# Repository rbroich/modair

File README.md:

# ModAir
Modular Aviation Instruments - Open Source Avionics for Microlights and other Non-Type-Certified Aircraft

For documentation and details refer to the Hackaday.io Project Page [ModAir - Modular Aviation Instruments](https://hackaday.io/project/19325)

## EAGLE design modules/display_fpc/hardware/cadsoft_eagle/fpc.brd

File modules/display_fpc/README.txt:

ERC240160_ENCLOSURE

rotary encoder: solder ribbon cable
(mounted to PCB would have insufficient reach, and mechanically difficult to insert with the LCD FPC soldered on already)

add SPDT switch on left side
and LED?

Fine grid sand paper on top
Printed front panel labels on thick transparency (guerrilla glass?)
-black portions to cover 3d printed inconsistencies

PCB:
-no components on bottom side, besides BUS connector
-header for LCD backlight
-LCD FPC footprint directly below LCD, inline with edge of LCD frame
-header for rotary encoder
-solder pads for switch
-electrolytic caps mounted sideways

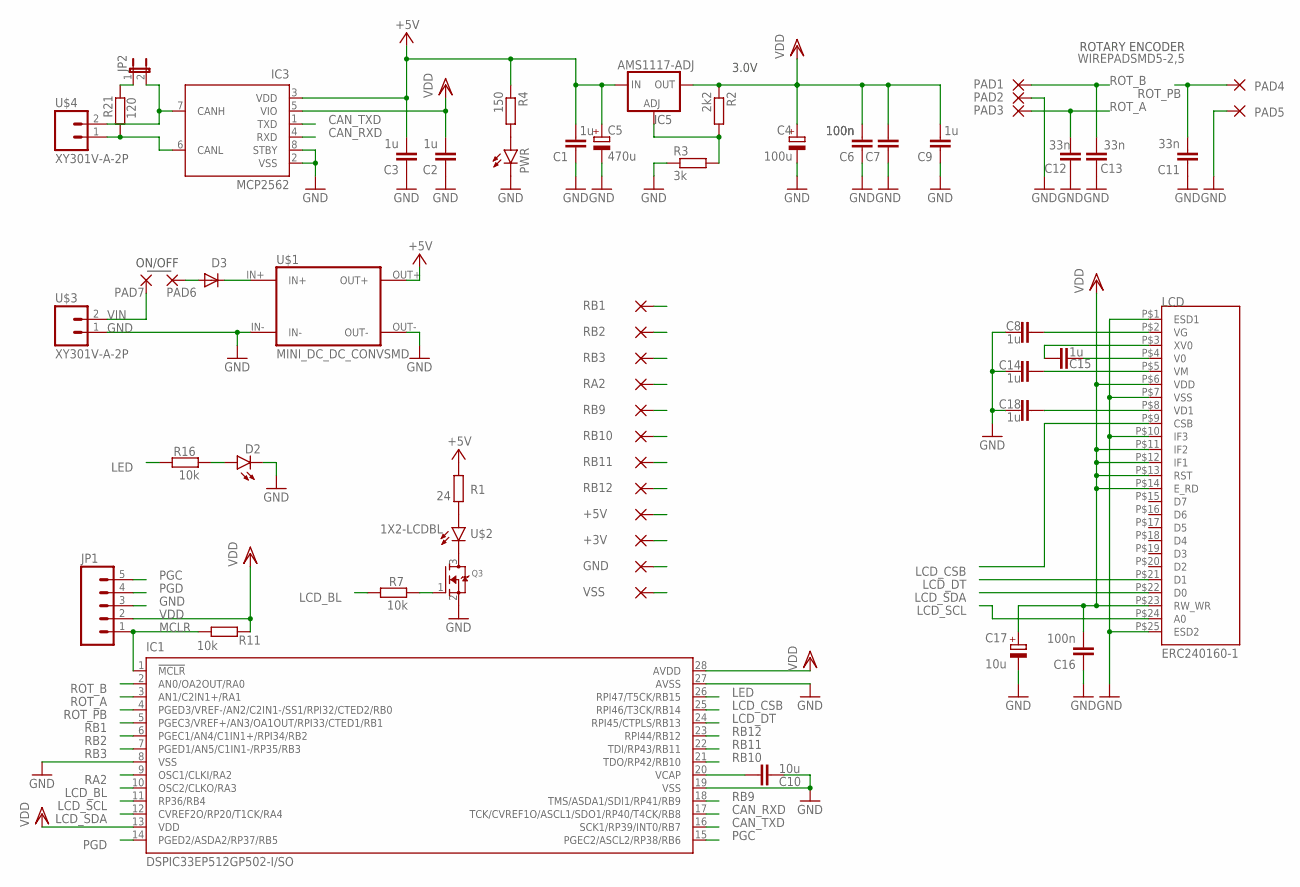
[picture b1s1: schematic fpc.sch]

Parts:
+3V, +5V: WIREPADSMD1,27-254; SMD1,27-2,54
C1, C2, C3, C8, C9, C14, C15, C18: 1u; C0603K
C4: 100u; SANYO-OSCON_SMD_B6
C5: 470u; SANYO-OSCON_SMD_B6
C6, C7, C16: 100n; C0603K
C10: 10u; C0805
C11, C12, C13: 33n; C0603K
C17: 10u; SANYO-OSCON_SMD_E12
D2: LED-FKIT-1206; FKIT-LED-1206
D3: DIODESMA; SMADIODE
GND: WIREPADSMD1,27-254; SMD1,27-2,54
IC1: DSPIC33EP512GP502-I/SO; SO28W
IC3: MCP2562; SO-08
IC5: AMS1117-ADJ; SOT223
JP1: M05PTH; 1X05
JP2: JP1E; JP1
LCD: ERC240160-1; 1X25-LCDFPC-SMD
PAD1, PAD2, PAD3, PAD4, PAD5, PAD6, PAD7: WIREPADSMD5-2,5; 5-2,5
PWR: LED-FKIT-1206; FKIT-LED-1206
Q3: MOSFET-NREFLOW; SOT23
R1: 24; R0805
R2: 2k2; R0603
R3: 3k; R0603
R4: 150; R0603
R7, R11, R16: 10k; R0603
R21: 120; R0603
RA2: WIREPADSMD1,27-254; SMD1,27-2,54
RB1, RB2, RB3, RB9, RB10, RB11, RB12: WIREPADSMD1,27-254; SMD1,27-2,54
U$1: MINI_DC_DC_CONVSMD; DSN-MINI-360-SMD
U$2: 1X2-LCDBL; 1X2-LCDBL-SMD
U$3, U$4: XY301V-A-2P
VSS: WIREPADSMD1,27-254; SMD1,27-2,54

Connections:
+5V: +5V.1, C1.2, C3.2, C5.+, IC3.3 (VDD), IC5.3 (IN), R1.1, R4.1, U$1.OUT+
CAN_H: IC3.7 (CANH), JP2.2, U$4.2
CAN_L: IC3.6 (CANL), R21.1, U$4.1
CAN_RXD: IC1.17 (TCK/CVREF1O/ASCL1/SDO1/RP40/T4CK/RB8), IC3.4 (RXD)
CAN_TXD: IC1.16 (SCK1/RP39/INT0/RB7), IC3.1 (TXD)
GND: C1.1, C2.1, C3.1, C4.-, C5.-, C6.1, C7.1, C8.1, C9.1, C10.1, C11.1, C12.1, C13.1, C14.1, C16.1, C17.-, C18.1, D2.C, GND.1, IC1.8 (VSS), IC1.19 (VSS), IC1.27 (AVSS), IC3.2 (VSS), IC3.8 (STBY), JP1.3, LCD.P$1 (ESD1), LCD.P$7 (VSS), LCD.P$10 (IF3), LCD.P$25 (ESD2), PAD2.1, PAD5.1, PWR.C, Q3.2 (S), R3.1, U$1.IN-, U$1.OUT-, U$3.1, VSS.1
LCD_BL: IC1.10 (OSC2/CLKO/RA3), R7.2
LCD_CSB: IC1.25 (RPI46/T3CK/RB14), LCD.P$9 (CSB)
LCD_DT: IC1.24 (RPI45/CTPLS/RB13), LCD.P$21 (D1)
LCD_SCL: IC1.11 (RP36/RB4), LCD.P$24 (A0)
LCD_SDA: IC1.12 (CVREF2O/RP20/T1CK/RA4), LCD.P$22 (D0)
LED: IC1.26 (RPI47/T5CK/RB15), R16.2
MCLR: IC1.1 (!MCLR!), JP1.1, R11.2
unnamed: Q3.1 (G), R7.1
unnamed: R1.2, U$2.A
unnamed: PWR.A, R4.2
unnamed: Q3.3 (D), U$2.K (C)
unnamed: C15.2, LCD.P$4 (V0)
unnamed: C15.1, LCD.P$3 (XV0)
unnamed: C8.2, LCD.P$2 (VG)
unnamed: C14.2, LCD.P$5 (VM)
unnamed: D2.A, R16.1
unnamed: C18.2, LCD.P$8 (VD1)
unnamed: IC5.1 (ADJ), R2.2, R3.2
unnamed: D3.A, PAD6.1
unnamed: JP2.1, R21.2
PGC: IC1.15 (PGEC2/ASCL2/RP38/RB6), JP1.5
PGD: IC1.14 (PGED2/ASDA2/RP37/RB5), JP1.4
RA2: IC1.9 (OSC1/CLKI/RA2), RA2.1
RB1: IC1.5 (PGEC3/VREF+/AN3/OA1OUT/RPI33/CTED1/RB1), RB1.1
RB2: IC1.6 (PGEC1/AN4/C1IN1+/RPI34/RB2), RB2.1
RB3: IC1.7 (PGED1/AN5/C1IN1-/RP35/RB3), RB3.1
RB9: IC1.18 (TMS/ASDA1/SDI1/RP41/RB9), RB9.1
RB10: IC1.21 (TDO/RP42/RB10), RB10.1
RB11: IC1.22 (TDI/RP43/RB11), RB11.1
RB12: IC1.23 (RPI44/RB12), RB12.1
ROT_A: C12.2, IC1.3 (AN1/C2IN1+/RA1), PAD3.1
ROT_B: C13.2, IC1.2 (AN0/OA2OUT/RA0), PAD1.1
ROT_PB: C11.2, IC1.4 (PGED3/VREF-/AN2/C2IN1-/SS1/RPI32/CTED2/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), PAD4.1
VCAP: C10.2, IC1.20 (VCAP)
VDD: +3V.1, C2.2, C4.+, C6.2, C7.2, C9.2, C16.2, C17.+, IC1.13 (VDD), IC1.28 (AVDD), IC3.5 (VIO), IC5.2 (OUT), IC5.@2 (OUT), JP1.2, LCD.P$6 (VDD), LCD.P$11 (IF2), LCD.P$12 (IF1), LCD.P$13 (RST), LCD.P$14 (E_RD), LCD.P$23 (RW_WR), R2.1, R11.1
VIN: PAD7.1, U$3.2
VIN_D: D3.C, U$1.IN+

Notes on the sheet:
3.0V
ON/OFF
ROTARY ENCODER

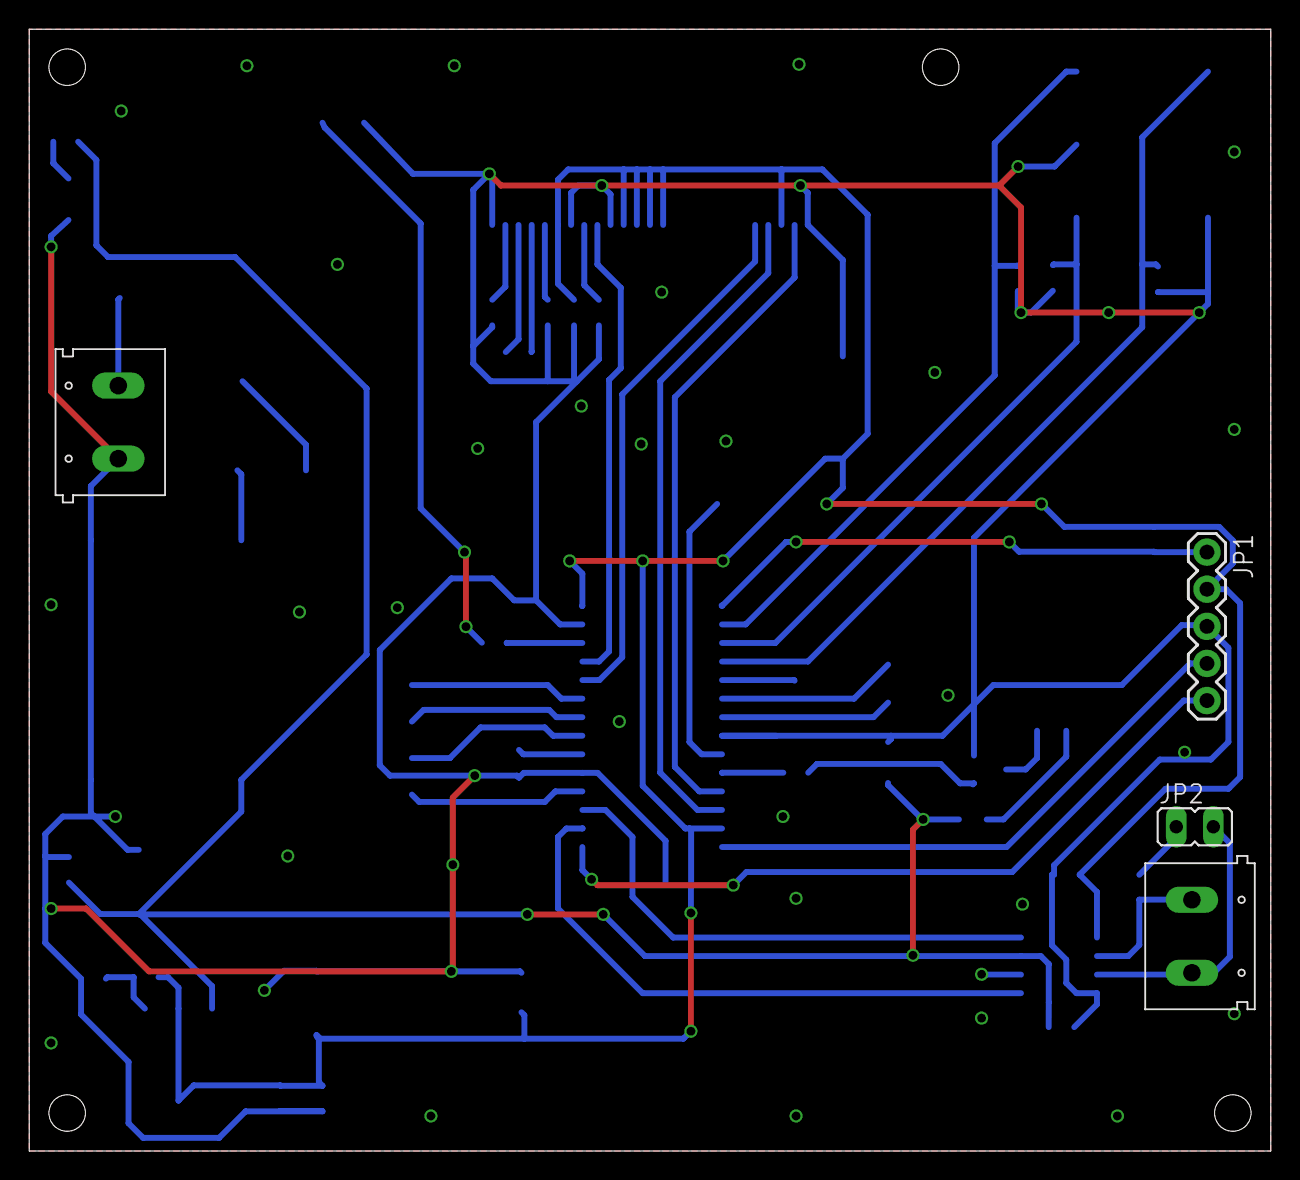
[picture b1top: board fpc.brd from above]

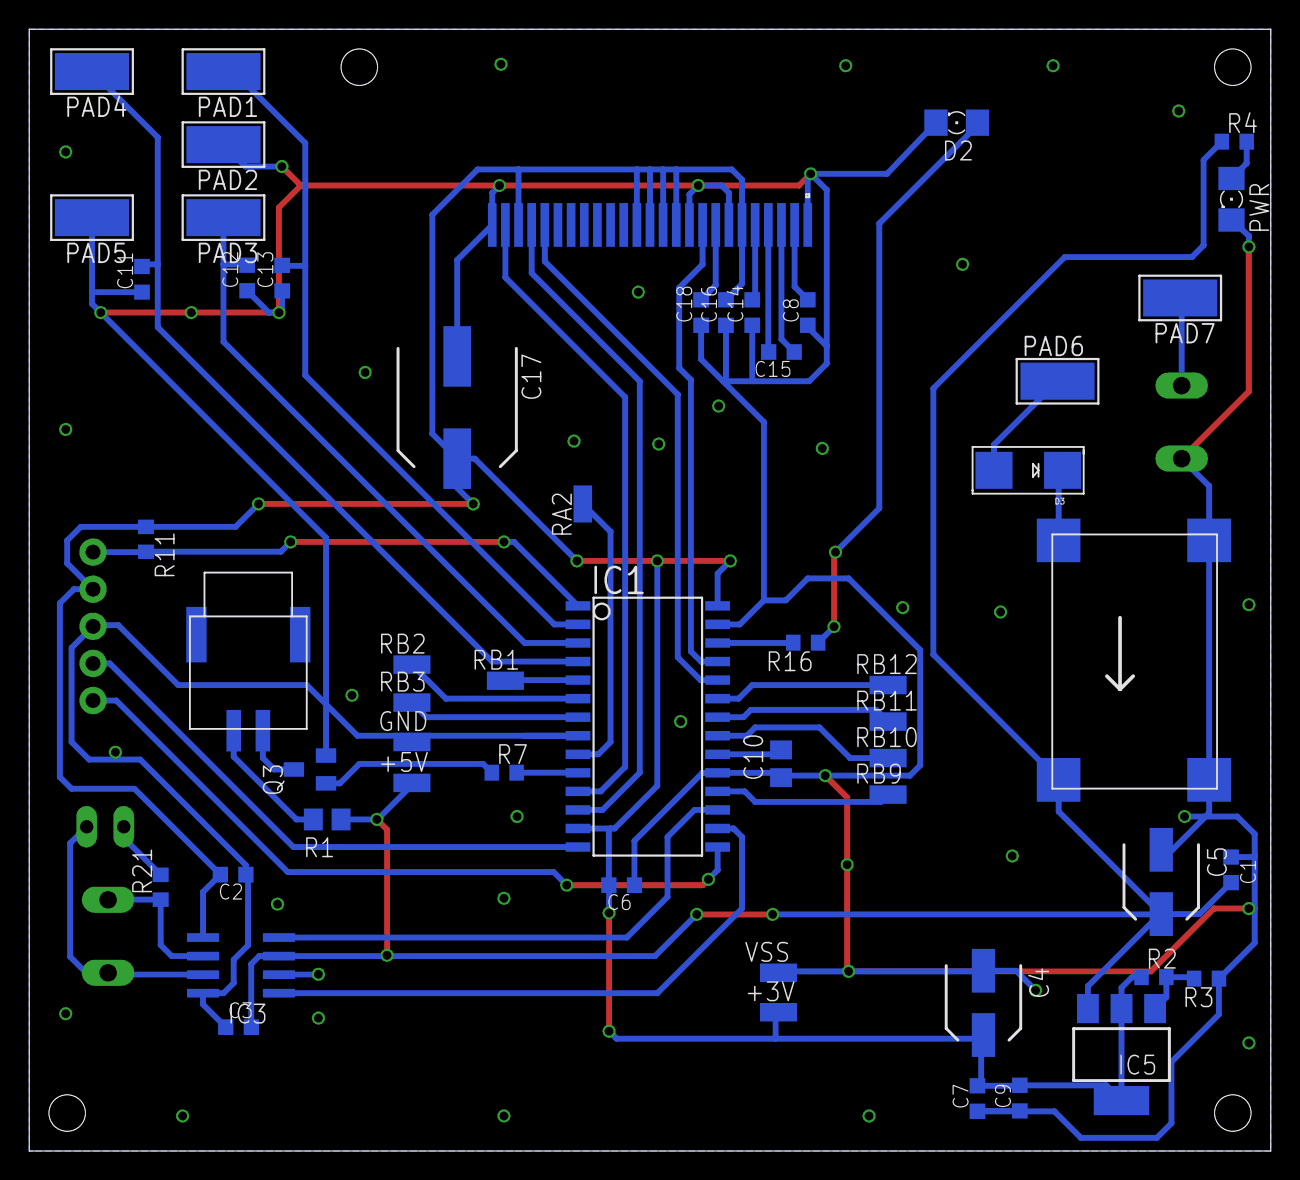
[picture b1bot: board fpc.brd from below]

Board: 2 copper layers, 85.0 x 76.8 mm, 59 parts (55 on the bottom side), 43 nets.

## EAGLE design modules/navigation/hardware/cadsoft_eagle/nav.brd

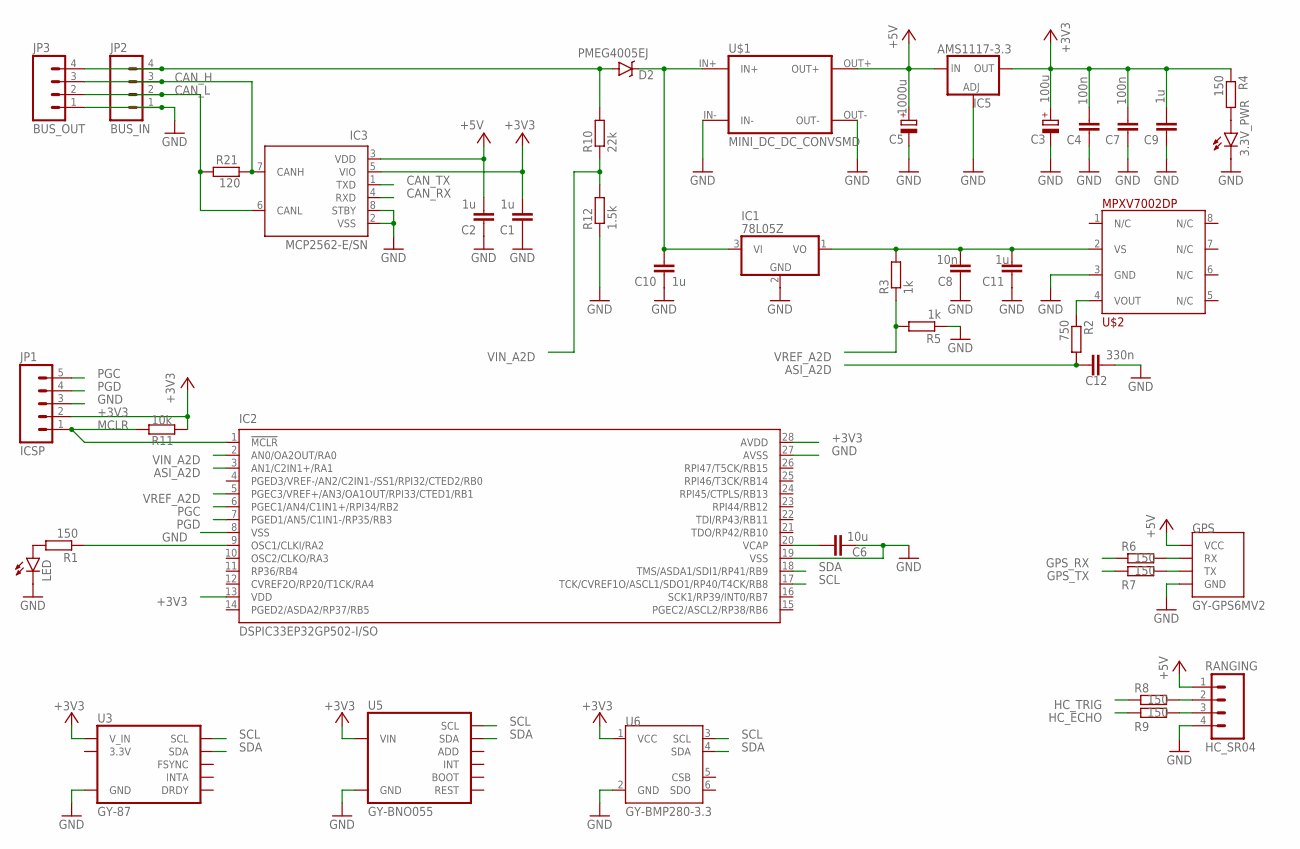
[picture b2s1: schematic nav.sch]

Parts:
3.3V_PWR: LED-FKIT-1206; FKIT-LED-1206
C1, C2, C11: 1u; C0603K
C3: 100u; E2,5-7
C4, C7: 100n; C0603K
C5: 1000u; E3,5-8
C6: 10u; C0805K
C8: 10n; C0603K
C9, C10: 1u; C0603
C12: 330n; C0603K
D2: PMEG4005EJ; SOD-323
GPS: GY-GPS6MV2
IC1: 78L05Z; TO92
IC2: DSPIC33EP32GP502-I/SO; SO28W
IC3: MCP2562-E/SN; SO-08
IC5: AMS1117-3.3; SOT223
JP1: ICSP; 1X05
JP2: BUS_IN; 1X04
JP3: BUS_OUT; 1X04
LED: LED-FKIT-1206; FKIT-LED-1206
R1, R4, R6, R7, R8, R9: 150; R0603
R2: 750; R0603
R3, R5: 1k; R0603
R10: 22k; R0603
R11: 10k; R0603
R12: 1.5k; R0603
R21: 120; R0603
RANGING: HC_SR04; 1X04
U3: GY-87
U5: GY-BNO055
U6: GY-BMP280-3.3
U$1: MINI_DC_DC_CONVSMD; DSN-MINI-360-SMD
U$2: MPXV7002DP

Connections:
3.3V: U3.3.3V
+3V3: C1.2, C3.+, C4.2, C7.2, C9.2, IC2.13 (VDD), IC2.28 (AVDD), IC3.5 (VIO), IC5.2 (OUT), IC5.@2 (OUT), JP1.2, R4.1, R11.1, U3.VCC_IN (V_IN), U5.VIN, U6.1 (VCC)
+5V: C2.2, C5.+, GPS.VCC, IC3.3 (VDD), IC5.3 (IN), RANGING.1, U$1.OUT+
ASI_A2D: C12.2, IC2.3 (AN1/C2IN1+/RA1), R2.2
CAN_H: IC3.7 (CANH), JP2.3, JP3.3, R21.2
CAN_L: IC3.6 (CANL), JP2.2, JP3.2, R21.1
CAN_RX: IC3.4 (RXD)
CAN_TX: IC3.1 (TXD)
GND: 3.3V_PWR.C, C1.1, C2.1, C3.-, C4.1, C5.-, C6.1, C7.1, C8.1, C9.1, C10.1, C11.1, C12.1, GPS.GND, IC1.2 (GND), IC2.8 (VSS), IC2.19 (VSS), IC2.27 (AVSS), IC3.2 (VSS), IC3.8 (STBY), IC5.1 (ADJ), JP1.3, JP2.1, JP3.1, LED.C, R5.1, R12.1, RANGING.4, U3.GND, U5.GND, U6.2 (GND), U$1.IN-, U$1.OUT-, U$2.3 (GND)
GPS_RX: R6.1
GPS_TX: R7.1
HC_ECHO: R9.1
HC_TRIG: R8.1
MCLR: IC2.1 (!MCLR!), JP1.1, R11.2
unnamed: C8.2, C11.2, IC1.1 (VO), R3.2, U$2.2 (VS)
unnamed: GPS.RX, R6.2
unnamed: 3.3V_PWR.A, R4.2
unnamed: LED.A, R1.2
unnamed: R2.1, U$2.4 (VOUT)
unnamed: GPS.TX, R7.2
unnamed: R8.2, RANGING.2
unnamed: R9.2, RANGING.3
unnamed: IC2.9 (OSC1/CLKI/RA2), R1.1
PGC: IC2.6 (PGEC1/AN4/C1IN1+/RPI34/RB2), JP1.5
PGD: IC2.7 (PGED1/AN5/C1IN1-/RP35/RB3), JP1.4
SCL: IC2.17 (TCK/CVREF1O/ASCL1/SDO1/RP40/T4CK/RB8), U3.SCL, U5.SCL, U6.3 (SCL)
SDA: IC2.18 (TMS/ASDA1/SDI1/RP41/RB9), U3.SDA, U5.SDA, U6.4 (SDA)
VCAP: C6.2, IC2.20 (VCAP)
VIN: D2.A, JP2.4, JP3.4, R10.2
VIN_A2D: IC2.2 (AN0/OA2OUT/RA0), R10.1, R12.2
VIN_D: C10.2, D2.C, IC1.3 (VI), U$1.IN+
VREF_A2D: IC2.5 (PGEC3/VREF+/AN3/OA1OUT/RPI33/CTED1/RB1), R3.1, R5.2

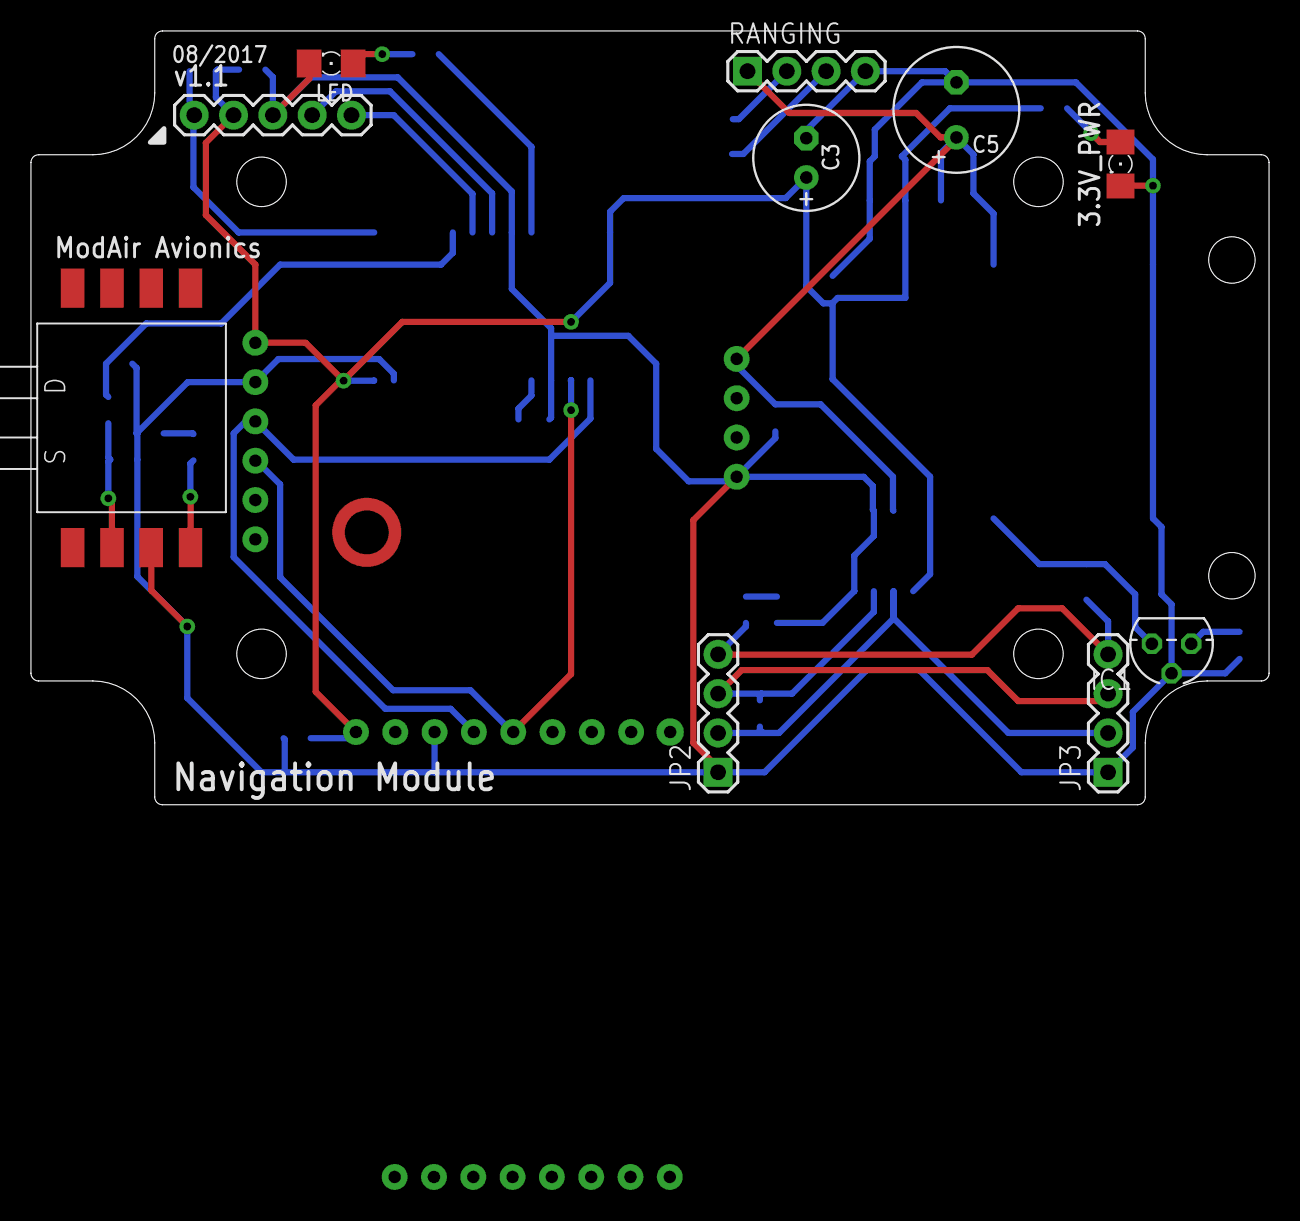
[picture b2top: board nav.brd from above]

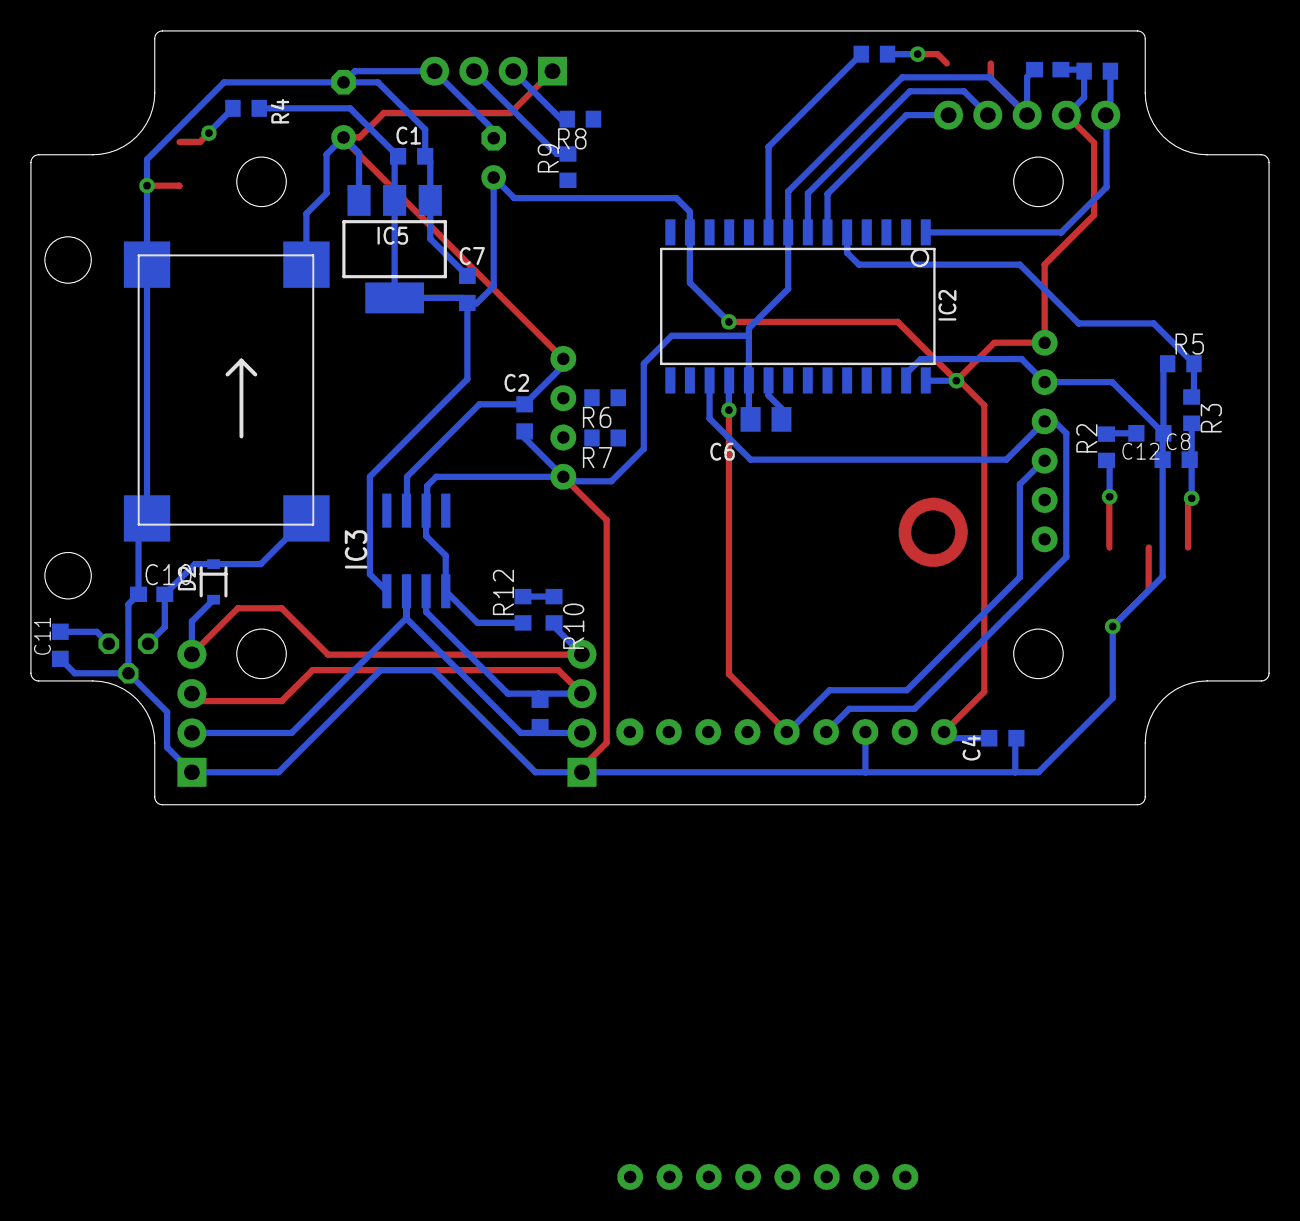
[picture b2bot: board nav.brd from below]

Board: 2 copper layers, 80.0 x 50.0 mm, 42 parts (29 on the bottom side), 25 nets.

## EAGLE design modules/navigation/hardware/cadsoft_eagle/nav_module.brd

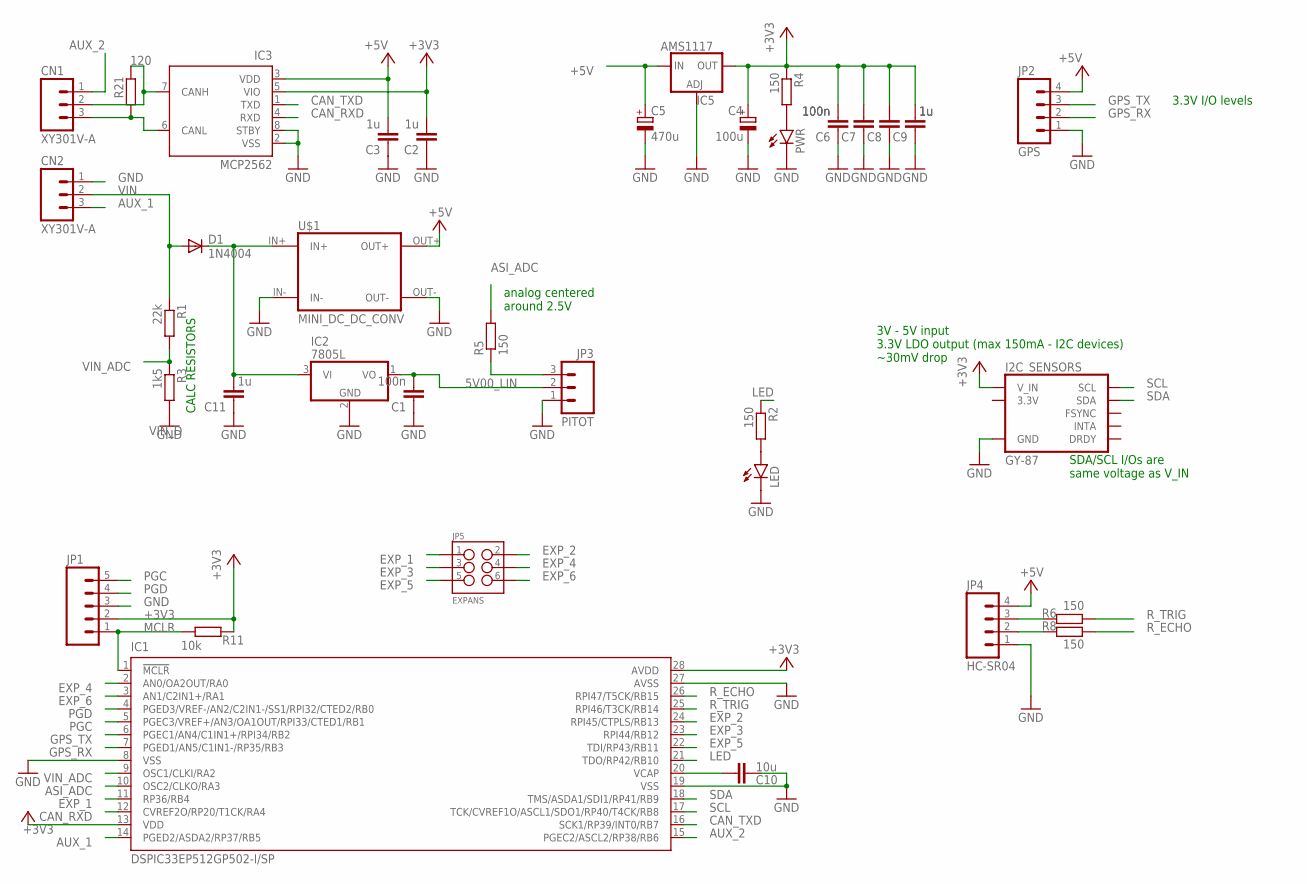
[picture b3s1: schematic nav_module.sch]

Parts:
C1, C6, C7: 100n; C0603K
C2, C3, C8, C9, C11: 1u; C0603K
C4: 100u; E2,5-7
C5: 470u; E3,5-8
C10: 10u; C025-030X050
CN1, CN2: XY301V-A
D1: 1N4004; DO41-10
I2C_SENSORS: GY-87
IC1: DSPIC33EP512GP502-I/SP; DIL28-3
IC2: 7805L; TO92
IC3: MCP2562; DIL8
IC5: AMS1117; SOT223
JP1: M05PTH; 1X05
JP2: GPS; 1X04
JP3: PITOT; 1X03
JP4: HC-SR04; 1X04
JP5: EXPANS; 2X3
LED: LED-FKIT-1206; FKIT-LED-1206
PWR: LED-FKIT-1206; FKIT-LED-1206
R1: 22k; R0603
R2, R4, R5, R6, R8: 150; R0603
R3: 1k5; R0603
R11: 10k; R0603
R21: 120; R0603
U$1: MINI_DC_DC_CONV; DSN-MINI-360

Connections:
3.3V: I2C_SENSORS.3.3V
5V00_LIN: C1.2, IC2.1 (VO), JP3.2
+3V3: C2.2, C4.+, C6.2, C7.2, C8.2, C9.2, I2C_SENSORS.VCC_IN (V_IN), IC1.13 (VDD), IC1.28 (AVDD), IC3.5 (VIO), IC5.2 (OUT), IC5.@2 (OUT), JP1.2, R4.1, R11.1
+5V: C3.2, C5.+, IC3.3 (VDD), IC5.3 (IN), JP2.4, JP4.4, U$1.OUT+
ASI: JP3.3, R5.1
ASI_ADC: IC1.10 (OSC2/CLKO/RA3), R5.2
AUX_1: CN2.3, IC1.14 (PGED2/ASDA2/RP37/RB5)
AUX_2: CN1.1, IC1.15 (PGEC2/ASCL2/RP38/RB6)
CAN_H: CN1.2, IC3.7 (CANH), R21.2
CAN_L: CN1.3, IC3.6 (CANL), R21.1
CAN_RXD: IC1.12 (CVREF2O/RP20/T1CK/RA4), IC3.4 (RXD)
CAN_TXD: IC1.16 (SCK1/RP39/INT0/RB7), IC3.1 (TXD)
EXP_1: IC1.11 (RP36/RB4), JP5.1
EXP_2: IC1.24 (RPI45/CTPLS/RB13), JP5.2
EXP_3: IC1.23 (RPI44/RB12), JP5.3
EXP_4: IC1.2 (AN0/OA2OUT/RA0), JP5.4
EXP_5: IC1.22 (TDI/RP43/RB11), JP5.5
EXP_6: IC1.3 (AN1/C2IN1+/RA1), JP5.6
GND: C1.1, C2.1, C3.1, C4.-, C5.-, C6.1, C7.1, C8.1, C9.1, C10.1, C11.1, CN2.1, I2C_SENSORS.GND, IC1.8 (VSS), IC1.19 (VSS), IC1.27 (AVSS), IC2.2 (GND), IC3.2 (VSS), IC3.8 (STBY), IC5.1 (ADJ), JP1.3, JP2.1, JP3.1, JP4.1, LED.C, PWR.C, R3.2, U$1.IN-, U$1.OUT-
GPS_RX: IC1.7 (PGED1/AN5/C1IN1-/RP35/RB3), JP2.2
GPS_TX: IC1.6 (PGEC1/AN4/C1IN1+/RPI34/RB2), JP2.3
HS_ECHO: JP4.2, R8.1
HS_TRIG: JP4.3, R6.2
LED: IC1.21 (TDO/RP42/RB10), R2.1
MCLR: IC1.1 (!MCLR!), JP1.1, R11.2
unnamed: PWR.A, R4.2
unnamed: LED.A, R2.2
PGC: IC1.5 (PGEC3/VREF+/AN3/OA1OUT/RPI33/CTED1/RB1), JP1.5
PGD: IC1.4 (PGED3/VREF-/AN2/C2IN1-/SS1/RPI32/CTED2/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), JP1.4
R_ECHO: IC1.26 (RPI47/T5CK/RB15), R8.2
R_TRIG: IC1.25 (RPI46/T3CK/RB14), R6.1
SCL: I2C_SENSORS.SCL, IC1.17 (TCK/CVREF1O/ASCL1/SDO1/RP40/T4CK/RB8)
SDA: I2C_SENSORS.SDA, IC1.18 (TMS/ASDA1/SDI1/RP41/RB9)
VCAP: C10.2, IC1.20 (VCAP)
VIN: CN2.2, D1.A, R1.1
VIN_ADC: IC1.9 (OSC1/CLKI/RA2), R1.2, R3.1
VIN_D: C11.2, D1.C, IC2.3 (VI), U$1.IN+

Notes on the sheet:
3V - 5V input 3.3V LDO output (max 150mA - I2C devices) ~30mV drop
SDA/SCL I/Os are same voltage as V_IN
3.3V I/O levels
analog centered around 2.5V
CALC RESISTORS

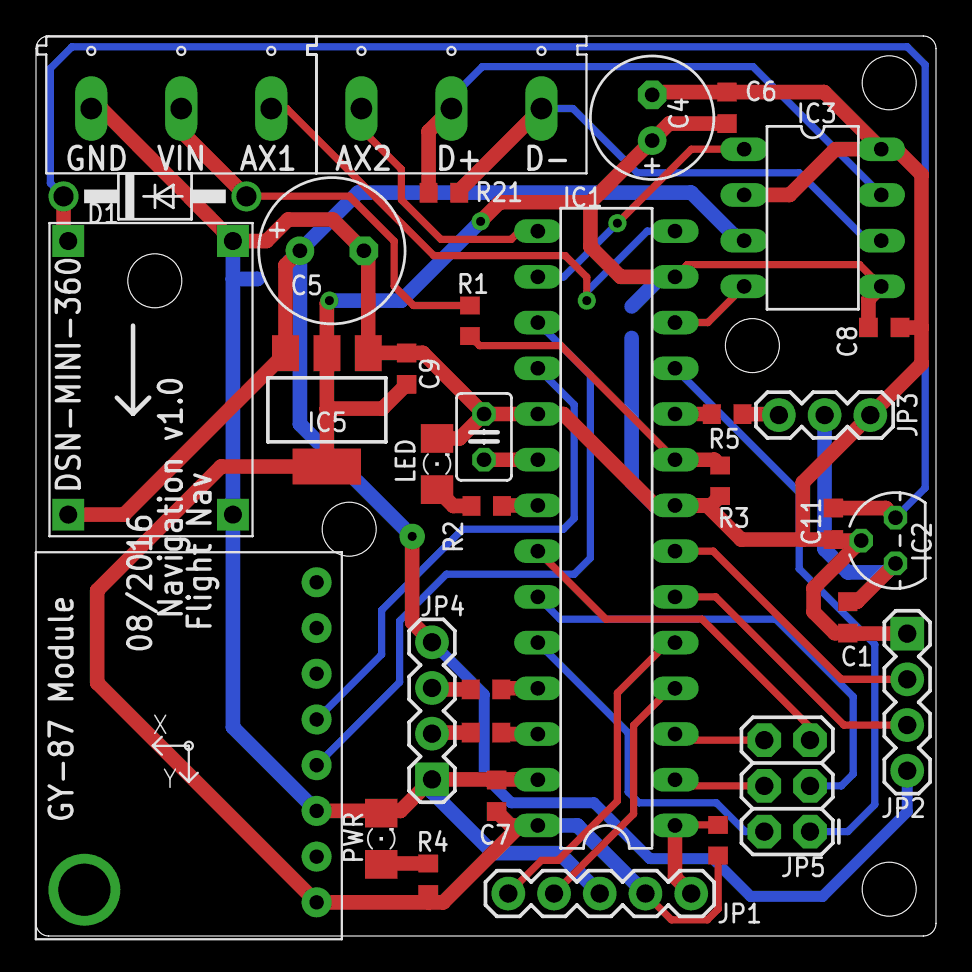
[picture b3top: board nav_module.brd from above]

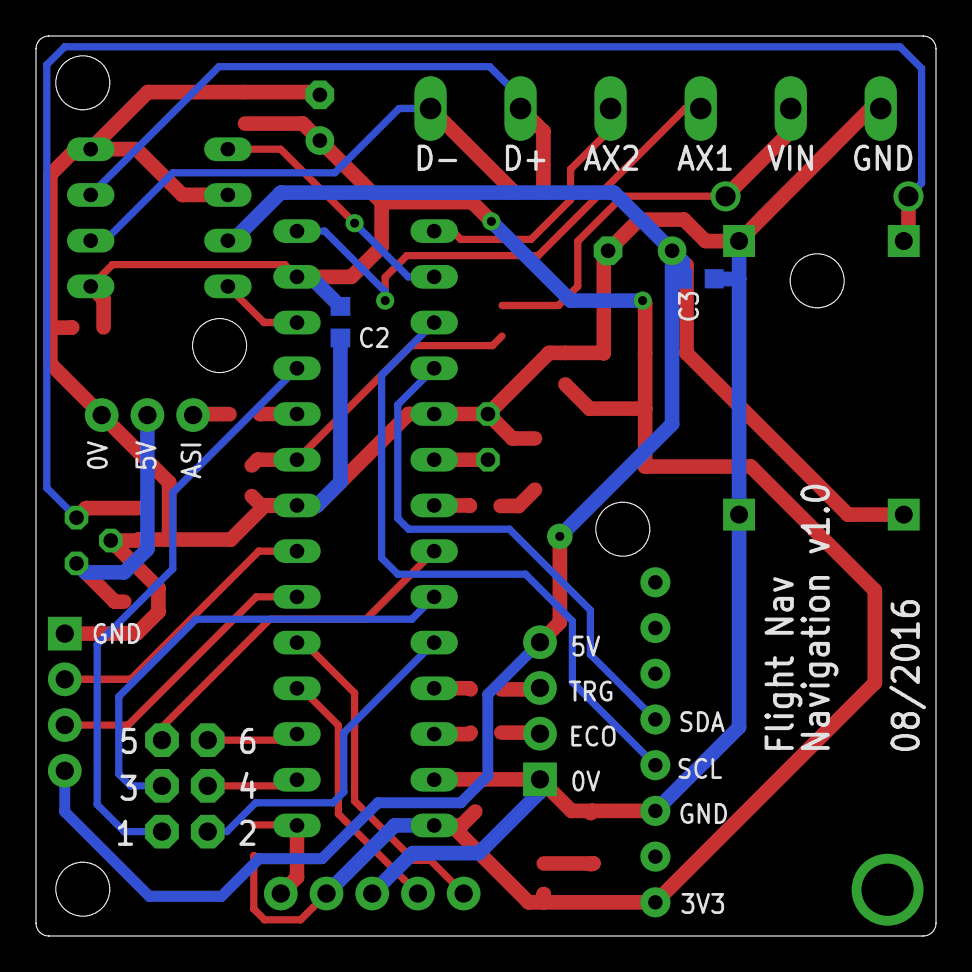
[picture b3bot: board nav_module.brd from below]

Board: 2 copper layers, 50.0 x 50.0 mm, 36 parts (2 on the bottom side), 36 nets.

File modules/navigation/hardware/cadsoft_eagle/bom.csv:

"Qty";"Value";"Device";"Package";"Parts";"Description";"PROD_ID";"VALUE";
"2";"";"LED-FKIT-1206";"FKIT-LED-1206";"LED, PWR";"LEDs";"";"";
"1";"";"M05PTH";"1X05";"JP1";"Header 5";"";"";
"3";"100n";"C-EUC0603K";"C0603K";"C1, C6, C7";"CAPACITOR, European symbol";"";"";
"1";"100u";"CPOL-EUE2.5-7";"E2,5-7";"C4";"POLARIZED CAPACITOR, European symbol";"";"";
"1";"10k";"R-EU_R0603";"R0603";"R11";"RESISTOR, European symbol";"";"";
"1";"10u";"C-EU025-030X050";"C025-030X050";"C10";"CAPACITOR, European symbol";"";"";
"1";"120";"R-EU_R0603";"R0603";"R21";"RESISTOR, European symbol";"";"";
"5";"150";"R-EU_R0603";"R0603";"R2, R4, R5, R6, R8";"RESISTOR, European symbol";"";"";
"1";"1N4004";"1N4004";"DO41-10";"D1";"DIODE";"";"";
"1";"1k5";"R-EU_R0603";"R0603";"R3";"RESISTOR, European symbol";"";"";
"5";"1u";"C-EUC0603K";"C0603K";"C2, C3, C8, C9, C11";"CAPACITOR, European symbol";"";"";
"1";"22k";"R-EU_R0603";"R0603";"R1";"RESISTOR, European symbol";"";"";
"1";"470u";"CPOL-EUE3.5-8";"E3,5-8";"C5";"POLARIZED CAPACITOR, European symbol";"";"";
"1";"7805L";"7805L";"TO92";"IC2";"Positive VOLTAGE REGULATOR";"";"";
"1";"AMS1117";"LD117AS33TR";"SOT223";"IC5";"Low drop fixed and adjustable positive voltage regulators 1 A";"";"";
"1";"DSPIC33EP512GP502-I/SP";"DSPIC33EP512GP502-I/SP";"DIL28-3";"IC1";"16-Bit Microcontrollers and Digital Signal Controllers";"";"";
"1";"EXPANS";"M03X2FEMALE";"2X3";"JP5";"2x3 .1" header.";"CONN-11566";"FEMALE 2x3";
"1";"GPS";"M04PTH";"1X04";"JP2";"Header 4";"";"";
"1";"GY-87";"GY-87";"GY-87";"I2C_SENSORS";"GY-87 10DOF MPU6050 HMC5883L BMP180 module";"";"";
"1";"HC-SR04";"M04PTH";"1X04";"JP4";"Header 4";"";"";
"1";"MCP2562";"MCP2562-E/P";"DIL8";"IC3";"High-Speed CAN Transceiver";"";"";
"1";"MINI_DC_DC_CONV";"MINI_DC_DC_CONV";"DSN-MINI-360";"U$1";"RC Airplane Module Mini 360 DC Buck Converter Step Down Module 4.75V-23V to 1V-17V 17x11x3.8mm New LM2596;";"";"";
"1";"PITOT";"M03PTH";"1X03";"JP3";"Header 3";"";"";
"2";"XY301V-A";"XY301V-A";"XY301V-A";"CN1, CN2";"3 Pin Screw Terminal Block Connector 5mm Pitch 5.08-301-3P 301-3P 3pin";"";"";

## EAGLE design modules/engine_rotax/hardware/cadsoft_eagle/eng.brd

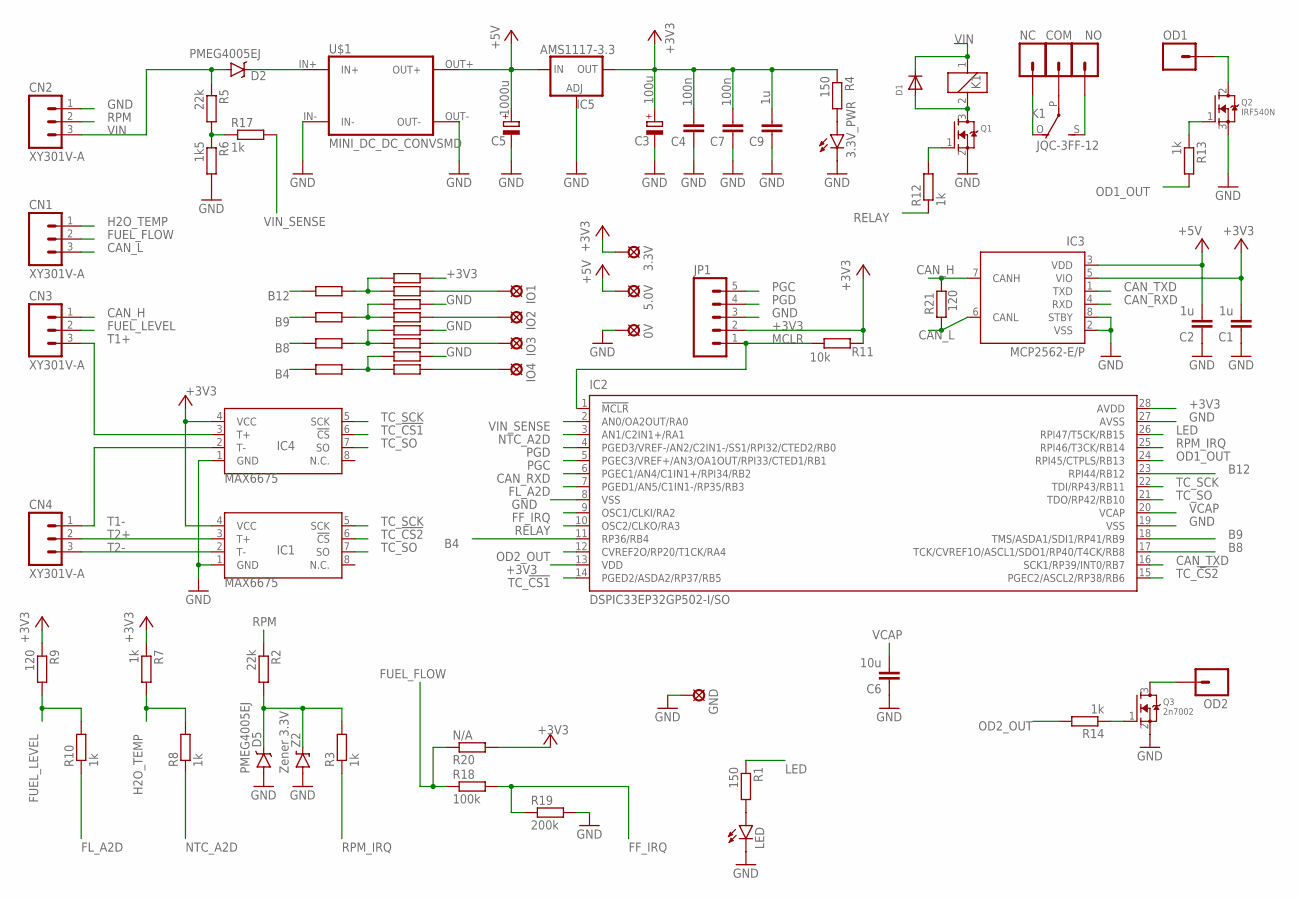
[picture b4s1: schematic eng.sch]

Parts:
0V, 3.3V, 5.0V: LSP10
3.3V_PWR: LED-FKIT-1206; FKIT-LED-1206
C1, C2: 1u; C0603K
C3: 100u; E2,5-7
C4, C7: 100n; C0603K
C5: 1000u; E3,5-8
C6: 10u; C3225
C9: 1u; C0603
CN1, CN2, CN3, CN4: XY301V-A
COM: M01PTH_LONGPAD; 1X01_LONGPAD
D1: DIODESMA; SMADIODE
D2, D5: PMEG4005EJ; SOD-323
GND: LSP10
IC1, IC4: MAX6675; SO08
IC2: DSPIC33EP32GP502-I/SO; SO28W
IC3: MCP2562-E/P; DIL8
IC5: AMS1117-3.3; SOT223
IO1, IO2, IO3, IO4: LSP10
JP1: M05PTH; 1X05
K1: JQC-3FF-12; G5LE
LED: LED-FKIT-1206; FKIT-LED-1206
NC: M01PTH_LONGPAD; 1X01_LONGPAD
NO: M01PTH_LONGPAD; 1X01_LONGPAD
OD1, OD2: M01PTH_LONGPAD; 1X01_LONGPAD
Q1: MOSFET-NREFLOW; SOT23
Q2: IRF540N; TO220V
Q3: 2n7002; SOT23
R1, R4: 150; R0603
R2, R5: 22k; R0603
R3, R7, R8, R10, R12, R13, R14, R17: 1k; R0603
R6: 1k5; R0603
R9, R21: 120; R0603
R11: 10k; R0603
R15, R16, R20, R23, R24, R25, R26, R29, R30, R31, R32, R35, R36: N/A; R0603
R18: 100k; R0603
R19: 200k; R0603
U$1: MINI_DC_DC_CONVSMD; DSN-MINI-360-SMD
Z2: Zener 3.3V; MINIMELF

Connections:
+3V3: 3.3V.MP, C1.2, C3.+, C4.2, C7.2, C9.2, IC1.4 (VCC), IC2.13 (VDD), IC2.28 (AVDD), IC3.5 (VIO), IC4.4 (VCC), IC5.2 (OUT), IC5.@2 (OUT), JP1.2, R4.1, R7.1, R9.1, R11.1, R20.2, R32.2
+5V: 5.0V.MP, C2.2, C5.+, IC3.3 (VDD), IC5.3 (IN), U$1.OUT+
B4: IC2.11 (RP36/RB4), R15.1
B8: IC2.17 (TCK/CVREF1O/ASCL1/SDO1/RP40/T4CK/RB8), R24.1
B9: IC2.18 (TMS/ASDA1/SDI1/RP41/RB9), R23.1
B12: IC2.23 (RPI44/RB12), R16.1
CAN_H: CN3.1, IC3.7 (CANH), R21.2
CAN_L: CN1.3, IC3.6 (CANL), R21.1
CAN_RXD: IC2.6 (PGEC1/AN4/C1IN1+/RPI34/RB2), IC3.4 (RXD)
CAN_TXD: IC2.16 (SCK1/RP39/INT0/RB7), IC3.1 (TXD)
FF_IRQ: IC2.9 (OSC1/CLKI/RA2), R18.2, R19.1
FL_A2D: IC2.7 (PGED1/AN5/C1IN1-/RP35/RB3), R10.1
FUEL_FLOW: CN1.2, R18.1, R20.1
FUEL_LEVEL: CN3.2, R9.2, R10.2
GND: 0V.MP, 3.3V_PWR.C, C1.1, C2.1, C3.-, C4.1, C5.-, C6.1, C7.1, C9.1, CN2.1, D5.A, GND.MP, IC1.1 (GND), IC2.8 (VSS), IC2.19 (VSS), IC2.27 (AVSS), IC3.2 (VSS), IC3.8 (STBY), IC4.1 (GND), IC5.1 (ADJ), JP1.3, LED.C, Q1.2 (S), Q2.3 (S), Q3.2 (S), R6.2, R19.2, R31.2, R35.2, R36.2, U$1.IN-, U$1.OUT-, Z2.A
H2O_TEMP: CN1.1, R7.2, R8.2
LED: IC2.26 (RPI47/T5CK/RB15), R1.1
MCLR: IC2.1 (!MCLR!), JP1.1, R11.2
unnamed: D1.A, K1.2, Q1.3 (D)
unnamed: Q1.1 (G), R12.2
unnamed: 3.3V_PWR.A, R4.2
unnamed: LED.A, R1.2
unnamed: Q2.1 (G), R13.1
unnamed: COM.1, K1.P
unnamed: K1.O, NC.1
unnamed: K1.S, NO.1
unnamed: OD1.1, Q2.2 (D)
unnamed: OD2.1, Q3.3 (D)
unnamed: Q3.1 (G), R14.1
unnamed: R15.2, R25.1, R31.1
unnamed: R16.2, R26.1, R32.1
unnamed: R5.2, R6.1, R17.1
unnamed: R23.2, R29.1, R35.1
unnamed: R24.2, R30.1, R36.1
unnamed: IO3.MP, R30.2
unnamed: IO2.MP, R29.2
unnamed: IO1.MP, R26.2
unnamed: IO4.MP, R25.2
NTC_A2D: IC2.3 (AN1/C2IN1+/RA1), R8.1
OD1_OUT: IC2.24 (RPI45/CTPLS/RB13), R13.2
OD2_OUT: IC2.12 (CVREF2O/RP20/T1CK/RA4), R14.2
PGC: IC2.5 (PGEC3/VREF+/AN3/OA1OUT/RPI33/CTED1/RB1), JP1.5
PGD: IC2.4 (PGED3/VREF-/AN2/C2IN1-/SS1/RPI32/CTED2/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), JP1.4
RELAY: IC2.10 (OSC2/CLKO/RA3), R12.1
RPM: CN2.2, R2.1
RPM_IRQ: IC2.25 (RPI46/T3CK/RB14), R3.1
RPM_Z: D5.C, R2.2, R3.2, Z2.C
T1+: CN3.3, IC4.3 (T+)
T1-: CN4.1, IC4.2 (T-)
T2+: CN4.2, IC1.3 (T+)
T2-: CN4.3, IC1.2 (T-)
TC_!CS1: IC2.14 (PGED2/ASDA2/RP37/RB5), IC4.6 (!CS)
TC_!CS2: IC1.6 (!CS), IC2.15 (PGEC2/ASCL2/RP38/RB6)
TC_SCK: IC1.5 (SCK), IC2.22 (TDI/RP43/RB11), IC4.5 (SCK)
TC_SO: IC1.7 (SO), IC2.21 (TDO/RP42/RB10), IC4.7 (SO)
VCAP: C6.2, IC2.20 (VCAP)
VIN: CN2.3, D1.C, D2.A, K1.1, R5.1
VIN_D: D2.C, U$1.IN+
VIN_SENSE: IC2.2 (AN0/OA2OUT/RA0), R17.2

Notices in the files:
parts and their libraries:
SparkFun-Connectors: Licensing: Creative Commons ShareAlike 4.0 International - https://creativecommons.org/licenses/by-sa/4.0
